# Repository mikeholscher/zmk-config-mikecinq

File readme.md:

# mikecinq keyboard by Mike Hölscher

This is just branch to build using ZMK main branch.

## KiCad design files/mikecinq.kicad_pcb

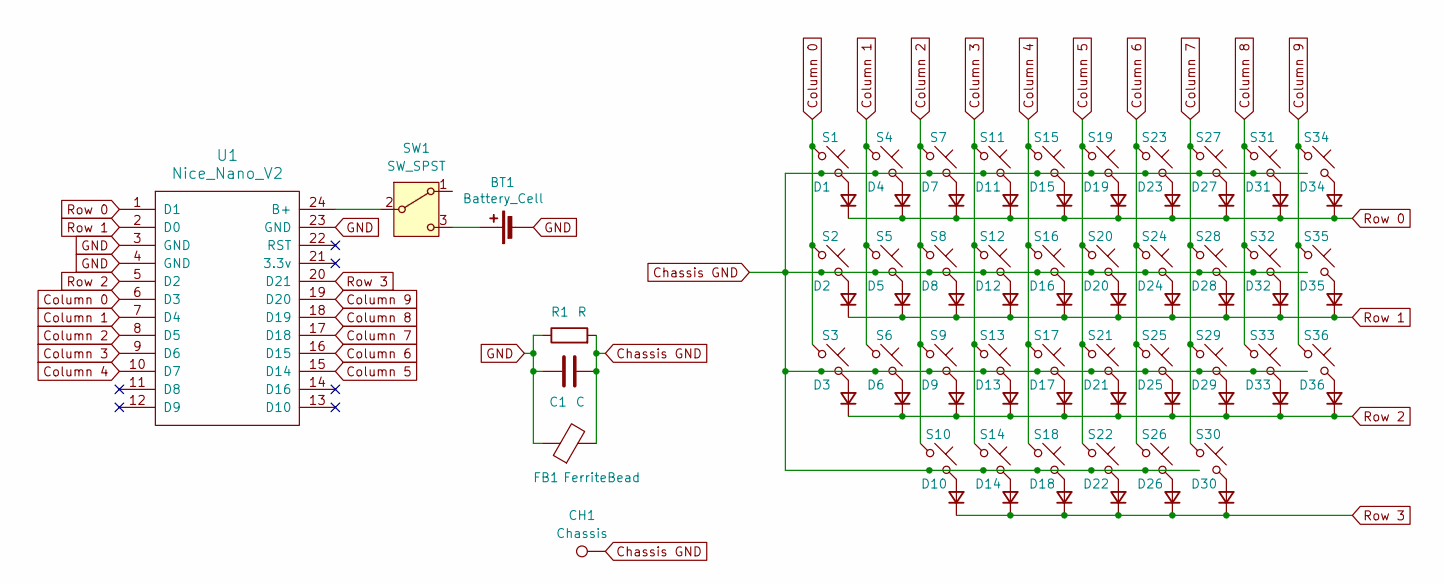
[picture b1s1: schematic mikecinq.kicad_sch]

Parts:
BT1: Battery_Cell; Battery_301230_Soldered
C1: C; C_0603_1608Metric
CH1: Chassis; Chassis GND
D1, D2, D3, D4, D5, D6, D7, D8, D9, D10, D11, D12, D13, D14, D15, D16, D17, D18, D19, D20, D21, D22, D23, D24, D25, D26, D27, D28, D29, D30, D31, D32, D33, D34, D35, D36: 1N4148WS; Diode_SOD-123; LCSC C2128
FB1: FerriteBead; L_0603_1608Metric
R1: R; R_0603_1608Metric
S1, S2, S3, S4, S5, S6, S7, S8, S9, S10, S11, S12, S13, S14, S15, S16, S17, S18, S19, S20, S21, S22, S23, S24, S25, S26, S27, S28, S29, S30, S31, S32, S33, S34, S35, S36: Keyswitch; CPG1316S01D02_handsolder
SW1: SW_SPST; MSK12C02
U1: Nice_Nano_V2; Nice_Nano_V2_Flat_Castelated

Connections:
Chassis GND: C1.2, CH1.1, FB1.2, R1.2, S1.3 (GND), S2.3 (GND), S3.3 (GND), S4.3 (GND), S5.3 (GND), S6.3 (GND), S7.3 (GND), S8.3 (GND), S9.3 (GND), S10.3 (GND), S11.3 (GND), S12.3 (GND), S13.3 (GND), S14.3 (GND), S15.3 (GND), S16.3 (GND), S17.3 (GND), S18.3 (GND), S19.3 (GND), S20.3 (GND), S21.3 (GND), S22.3 (GND), S23.3 (GND), S24.3 (GND), S25.3 (GND), S26.3 (GND), S27.3 (GND), S28.3 (GND), S29.3 (GND), S30.3 (GND), S31.3 (GND), S32.3 (GND), S33.3 (GND), S34.3 (GND), S35.3 (GND), S36.3 (GND)
Column 0: S1.1, S2.1, S3.1, U1.6 (D3)
Column 1: S4.1, S5.1, S6.1, U1.7 (D4)
Column 2: S7.1, S8.1, S9.1, S10.1, U1.8 (D5)
Column 3: S11.1, S12.1, S13.1, S14.1, U1.9 (D6)
Column 4: S15.1, S16.1, S17.1, S18.1, U1.10 (D7)
Column 5: S19.1, S20.1, S21.1, S22.1, U1.15 (D14)
Column 6: S23.1, S24.1, S25.1, S26.1, U1.16 (D15)
Column 7: S27.1, S28.1, S29.1, S30.1, U1.17 (D18)
Column 8: S31.1, S32.1, S33.1, U1.18 (D19)
Column 9: S34.1, S35.1, S36.1, U1.19 (D20)
GND: BT1.2 (-), C1.1, FB1.1, R1.1, U1.3 (GND), U1.4 (GND), U1.23 (GND)
unnamed: BT1.1 (+), SW1.3 (C)
unnamed: D1.2 (A), S1.2
unnamed: D2.2 (A), S2.2
unnamed: D3.2 (A), S3.2
unnamed: D4.2 (A), S4.2
unnamed: D5.2 (A), S5.2
unnamed: D6.2 (A), S6.2
unnamed: D7.2 (A), S7.2
unnamed: D8.2 (A), S8.2
unnamed: D9.2 (A), S9.2
unnamed: D10.2 (A), S10.2
unnamed: D11.2 (A), S11.2
unnamed: D12.2 (A), S12.2
unnamed: D13.2 (A), S13.2
unnamed: D14.2 (A), S14.2
unnamed: D15.2 (A), S15.2
unnamed: D16.2 (A), S16.2
unnamed: D17.2 (A), S17.2
unnamed: D18.2 (A), S18.2
unnamed: D19.2 (A), S19.2
unnamed: D20.2 (A), S20.2
unnamed: D21.2 (A), S21.2
unnamed: D22.2 (A), S22.2
unnamed: D23.2 (A), S23.2
unnamed: D24.2 (A), S24.2
unnamed: D25.2 (A), S25.2
unnamed: D26.2 (A), S26.2
unnamed: D27.2 (A), S27.2
unnamed: D28.2 (A), S28.2
unnamed: D29.2 (A), S29.2
unnamed: D30.2 (A), S30.2
unnamed: D31.2 (A), S31.2
unnamed: D32.2 (A), S32.2
unnamed: D33.2 (A), S33.2
unnamed: D34.2 (A), S34.2
unnamed: D35.2 (A), S35.2
unnamed: D36.2 (A), S36.2
unnamed: SW1.2 (B), U1.24 (B+)
Row 0: D1.1 (K), D4.1 (K), D7.1 (K), D11.1 (K), D15.1 (K), D19.1 (K), D23.1 (K), D27.1 (K), D31.1 (K), D34.1 (K), U1.1 (D1)
Row 1: D2.1 (K), D5.1 (K), D8.1 (K), D12.1 (K), D16.1 (K), D20.1 (K), D24.1 (K), D28.1 (K), D32.1 (K), D35.1 (K), U1.2 (D0)
Row 2: D3.1 (K), D6.1 (K), D9.1 (K), D13.1 (K), D17.1 (K), D21.1 (K), D25.1 (K), D29.1 (K), D33.1 (K), D36.1 (K), U1.5 (D2)
Row 3: D10.1 (K), D14.1 (K), D18.1 (K), D22.1 (K), D26.1 (K), D30.1 (K), U1.20 (D21)

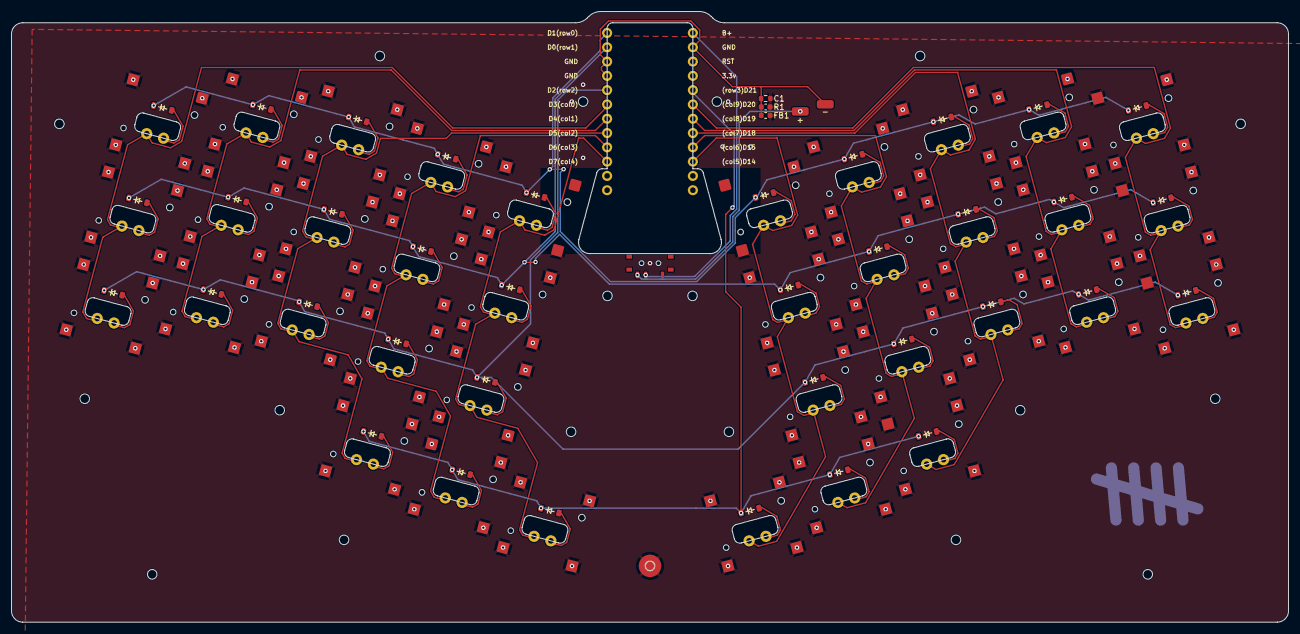
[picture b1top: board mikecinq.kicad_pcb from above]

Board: 2 copper layers, 226.9 x 108.5 mm, 79 parts (0 on the bottom side), 54 nets.

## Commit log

2025-07-17 general updates
2025-12-15 modified build.yaml and west.yml
2025-12-15 removed 'led_strip' in keymap
2025-12-15 removed rgb and added enter combo
2026-01-11 Single thumbs combo layout
2026-01-11 Autoshift Tapping term
2026-01-11 Forgot some Backspace thumbs
2026-01-11 Mistake in 4 in Num layer
2026-01-11 not on all layers
2026-01-12 Mac bindings
2026-01-13 Euro sign and option backspace
2026-01-24 plain qwerty test layer + Enter combo term mistake
2026-01-24 forgot system combo in plain base
2026-01-30 rupestris mistake
2026-03-05 cleaned up zmk main branch
2026-03-05 first zongle attempt
2026-03-06 initial test of board naming changes
2026-04-24 adding battery level reporting
2026-04-24 transparent interpunction on num layer
